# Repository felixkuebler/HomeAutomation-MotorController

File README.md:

# Introduction
Due to the growing demand of iot devices for home automation this project presents an cheap, easy to use and "open source" alternative to brand Products such as Phillips Hue. Based on the ESP8266-12E, a small WiFi enabled chipset, these devices can be retrofitted in a variety of devices such as light switches, motor controllers and more.

Each home automation node will access your local wifi network and is configurable through a webpage hosted locally on the device itsself. Your network needs to provide a [mqtt](https://pagefault.blog/2017/03/02/using-local-mqtt-broker-for-cloud-and-interprocess-communication/) broker to enable communication between nodes thus enabling its full functionality. An easy to use webinterface as well as a mqtt broker is provided by [Openhab](https://www.openhab.org/).

# Motor Controller
This small module can be mounted on any [Nema17](http://reprap.org/wiki/NEMA_17_Stepper_motor) stepper motor and thereby enabling Wifi functionality. The built in [TMC2130](https://www.trinamic.com/) stepper driver provides virtually silent motor operation as well as resistance detection of the driveshaft. This feature eliminates the need for endstops or any other sensor inputs thus resulting in a small and easy to use form factor. 

The current versions can be found here:
* *no release available*

# License
This work is property of Felix Kübler and is licensed under the
<a rel="license" href="http://creativecommons.org/licenses/by-nc/4.0/">Creative Commons Attribution-NonCommercial 4.0 International License</a>.

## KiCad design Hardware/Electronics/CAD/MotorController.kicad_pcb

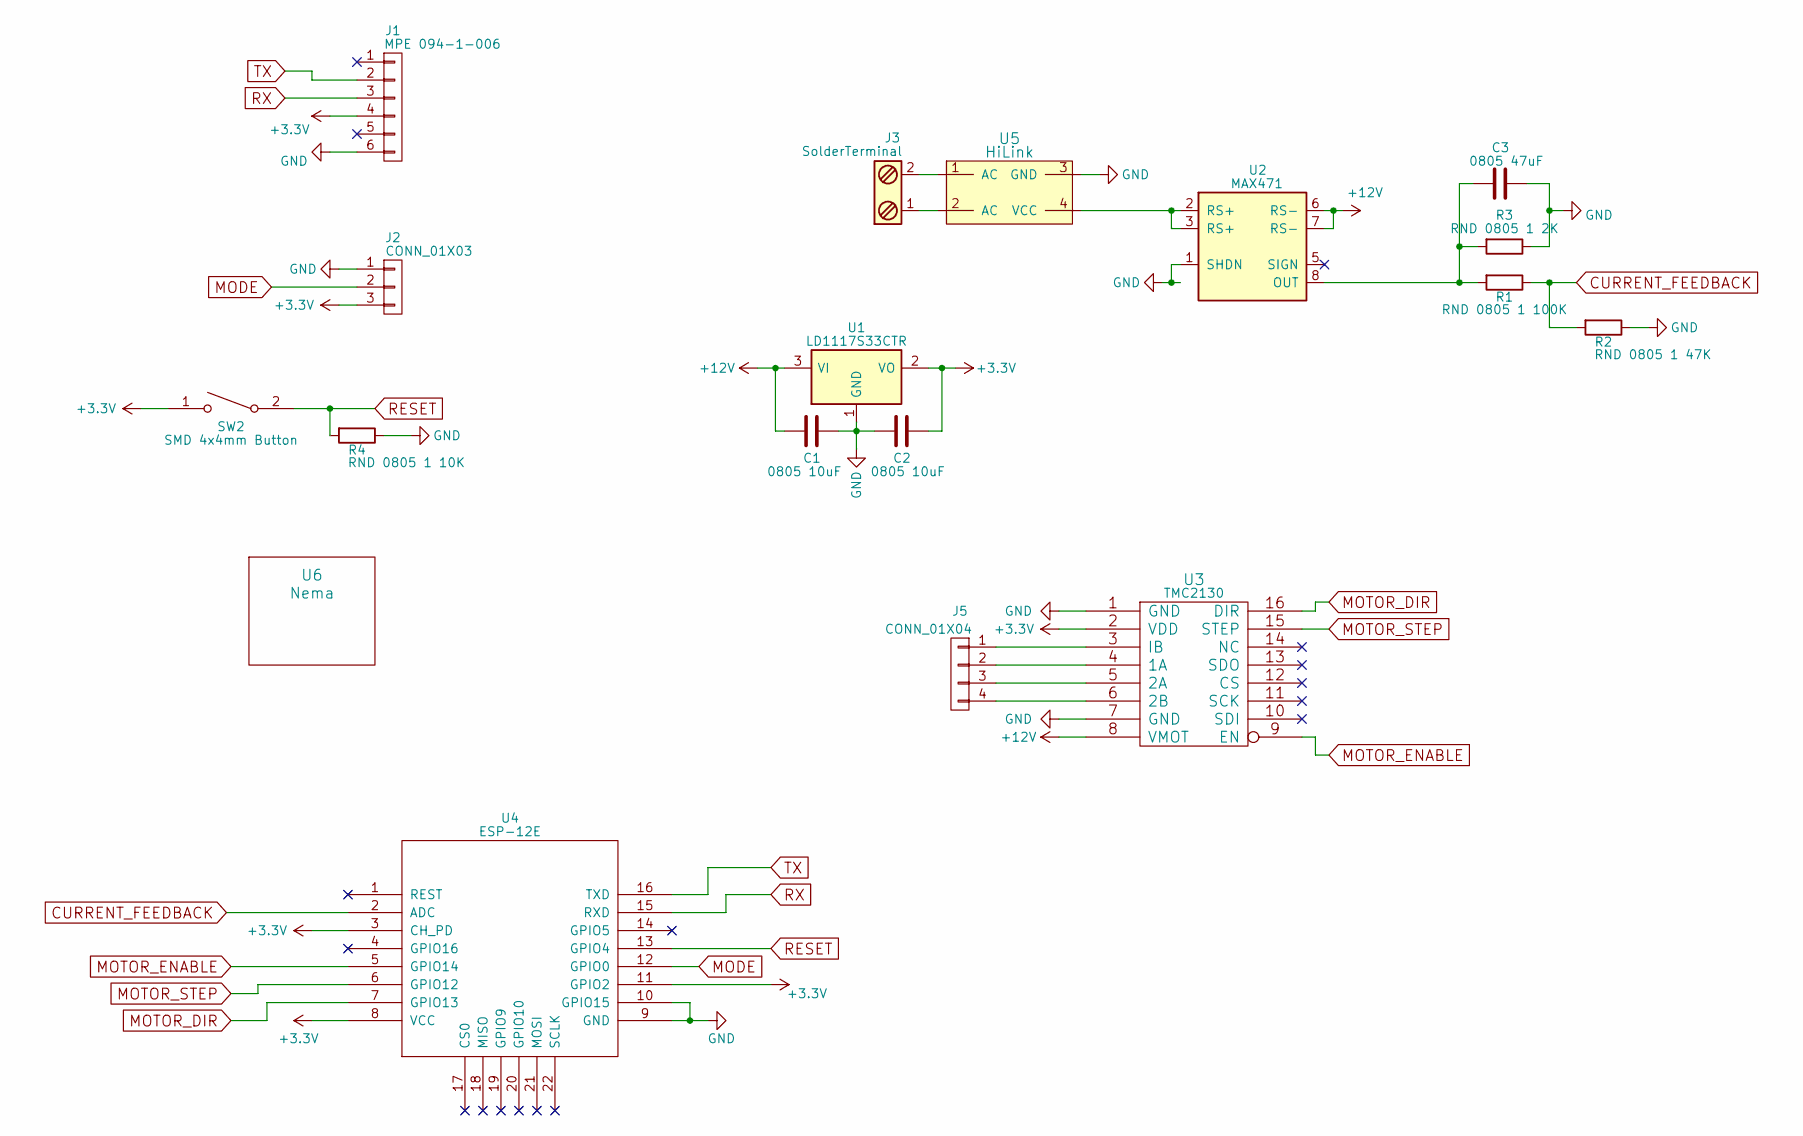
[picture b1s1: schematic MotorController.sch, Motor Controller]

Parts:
C1, C2: 0805 10uF; C_0805
C3: 0805 47uF; C_0805
J1: MPE 094-1-006; Pin_Header_Straight_1x06_Pitch2.54mm_SMD_Pin1Right
J2: CONN_01X03; Pin_Header_Straight_1x03_Pitch2.54mm_SMD_Pin1Right
J3: SolderTerminal; SolderPad_1x2_2.54mm
J5: CONN_01X04; Pin_Header_SMD_1x4_Angled_2.54mm
R1: RND 0805 1 100K; R_0805
R2: RND 0805 1 47K; R_0805
R3: RND 0805 1 2K; R_0805
R4: RND 0805 1 10K; R_0805
SW2: SMD 4x4mm Button; SW_SPST_SKQG
U1: LD1117S33CTR; SOT-223
U2: MAX471; SOIC-8_3.9x4.9mm_Pitch1.27mm
U3: TMC2130; TMC2230_SMD
U4: ESP-12E; ESP-12E_SMD
U5: HiLink; HLK-PM01
U6: Nema; Nema17

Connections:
+3V3: C2.1, J1.4, J2.3, SW2.1, U1.2 (VO), U3.2 (VDD), U4.3 (CH_PD), U4.8 (VCC), U4.11 (GPIO2)
+12V: C1.2, U1.3 (VI), U2.6 (RS-), U2.7 (RS-), U3.8 (VMOT)
CURRENT_FEEDBACK: R1.1, R2.2, U4.2 (ADC)
GND: C1.1, C2.2, C3.1, J1.6, J2.1, R2.1, R3.1, R4.1, U1.1 (GND), U2.1 (SHDN), U2.4 (GND), U3.1 (GND), U3.7 (GND), U4.9 (GND), U4.10 (GPIO15), U5.3 (GND)
MODE: J2.2, U4.12 (GPIO0)
MOTOR_DIR: U3.16 (DIR), U4.7 (GPIO13)
MOTOR_ENABLE: U3.9 (EN), U4.5 (GPIO14)
MOTOR_STEP: U3.15 (STEP), U4.6 (GPIO12)
unnamed: C3.2, R1.2, R3.2, U2.8 (OUT)
unnamed: J3.1, U5.2 (AC)
unnamed: J3.2, U5.1 (AC)
unnamed: J5.1, U3.3 (IB)
unnamed: J5.2, U3.4 (1A)
unnamed: J5.3, U3.5 (2A)
unnamed: J5.4, U3.6 (2B)
unnamed: U2.2 (RS+), U2.3 (RS+), U5.4 (VCC)
RESET: R4.2, SW2.2, U4.13 (GPIO4)
RX: J1.3, U4.15 (RXD)
TX: J1.2, U4.16 (TXD)

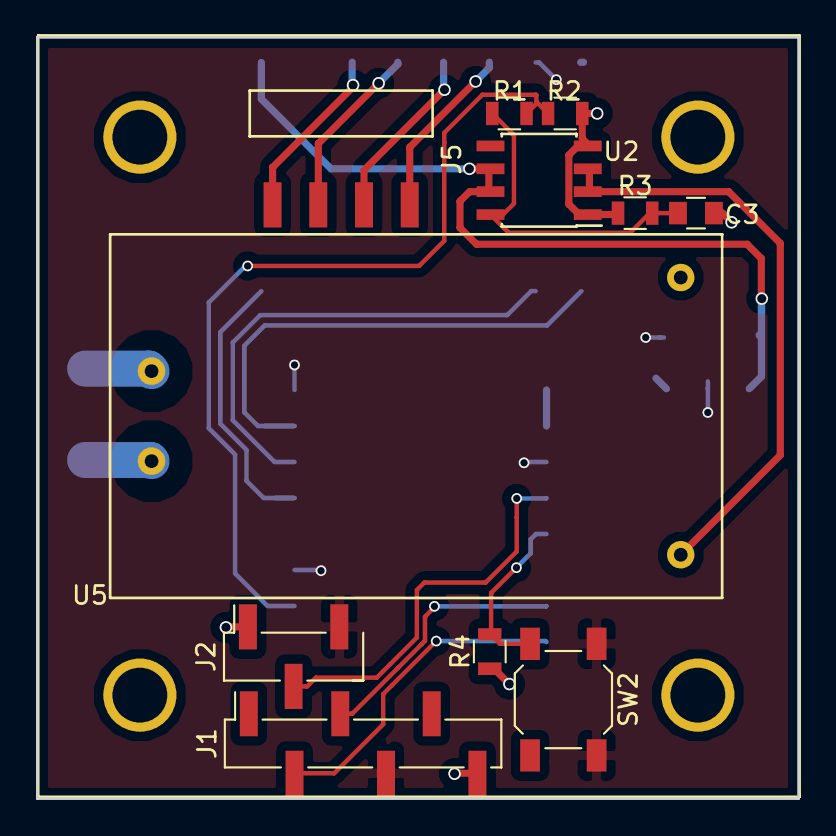
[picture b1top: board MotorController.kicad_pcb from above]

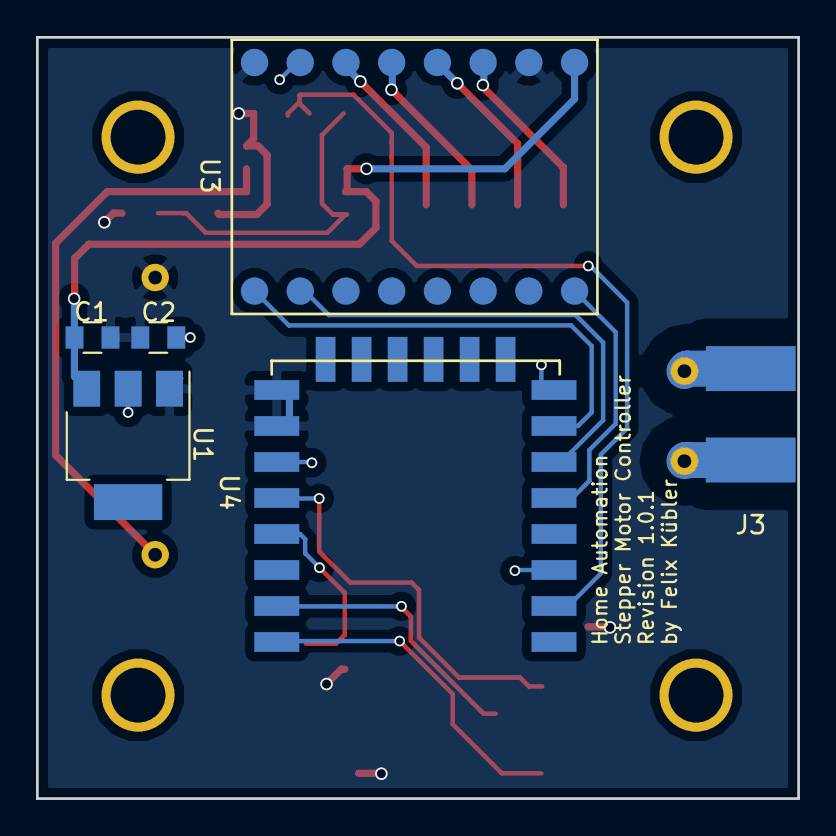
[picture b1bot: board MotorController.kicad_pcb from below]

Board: 2 copper layers, 42.3 x 42.3 mm, 18 parts (6 on the bottom side), 19 nets.

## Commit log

2018-02-15 motor controller single repo setup
2018-02-23 home automation iplementation of motor controller software
2018-03-23 specification added
2018-03-24 new software file structure
2018-03-24 introduction of basic setup files
2018-04-08 kicad linkage fix
2018-04-08 revision1.0.0 for electrical hardware
2018-06-03 library changes
2018-06-03 licensing
2018-06-03 gerber files
2018-06-03 new renderings
2018-06-28 test excel
2018-06-28 test
2018-06-28 test finished
2018-07-29 bug fix current sensor
2018-08-29 MAX741 missing resistor fix
2018-08-29 additional capacitor for current sensor smoothing
2018-09-01 part reference cleanup
2018-09-03 test assembly
2018-09-03 basic software setup more basic
2018-09-03 library linkage fix
2018-09-05 terminal footprints
2018-09-23 housing for pcb
2019-01-22 new gerber files
2022-10-22 add README
2022-10-22 rename Specifications to Datasheets
2022-10-23 rename software source and move tests in source
2022-10-23 rename tests
